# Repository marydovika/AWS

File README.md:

//////////////////////////////////////////////////////////////////////////////////////////////////

System Description:

Automatic Weather Stations (AWS) play a critical role in environmental monitoring, yet
their deployment in remote and energy-constrained locations remains limited by rigid and
monolithic power architectures.
Conventional systems are often designed for single energy sources, leading to inefficiencies, frequent power interruptions, high maintenance costs, and
poor adaptability to dynamic environmental conditions.
This research proposes the development of a modular and adaptive power electronics system architecture tailored for
energy-constrained AWS deployments.
Modular design;
The modular design introduces swappable converter topologies that allow scalable integration (multiplexing) of multiple energy sources,
including solar, DC input and  batteries, while simplifying upgrades, repairs, and fault isolation.
Adaptive design;
Complementing the modular design, an adaptive control strategy will be implemented to dynamically
optimize power flow in response to load variations, energy resource intermittency, in-system parameter drifts, and external/environmental
disturbances, thereby enhancing system stability and efficiency.
The study will involve system design, prototype development, and two algorithm development (both AMPC-based), followed by performance evaluation
under varying operating conditions and benchmarking. Field deployment of Final product (PCB, Case Unit, and Mounting frame).

Expected outcomes include;
improved system energy efficiency,
fault tolerance, and operational autonomy,
ensuring more reliable and sustainable weather data collection in energy resource-constrained and off-grid regions.
The findings of this research will contribute to advancing resilient power system solutions that support agriculture, public
safety, infrastructure planning, and climate research. with a civil and possible military adaptation.

Project is funded by:
https://www.ademneaproject.net

//////////////////////////////////////////////////////////////////////////////////////////////////

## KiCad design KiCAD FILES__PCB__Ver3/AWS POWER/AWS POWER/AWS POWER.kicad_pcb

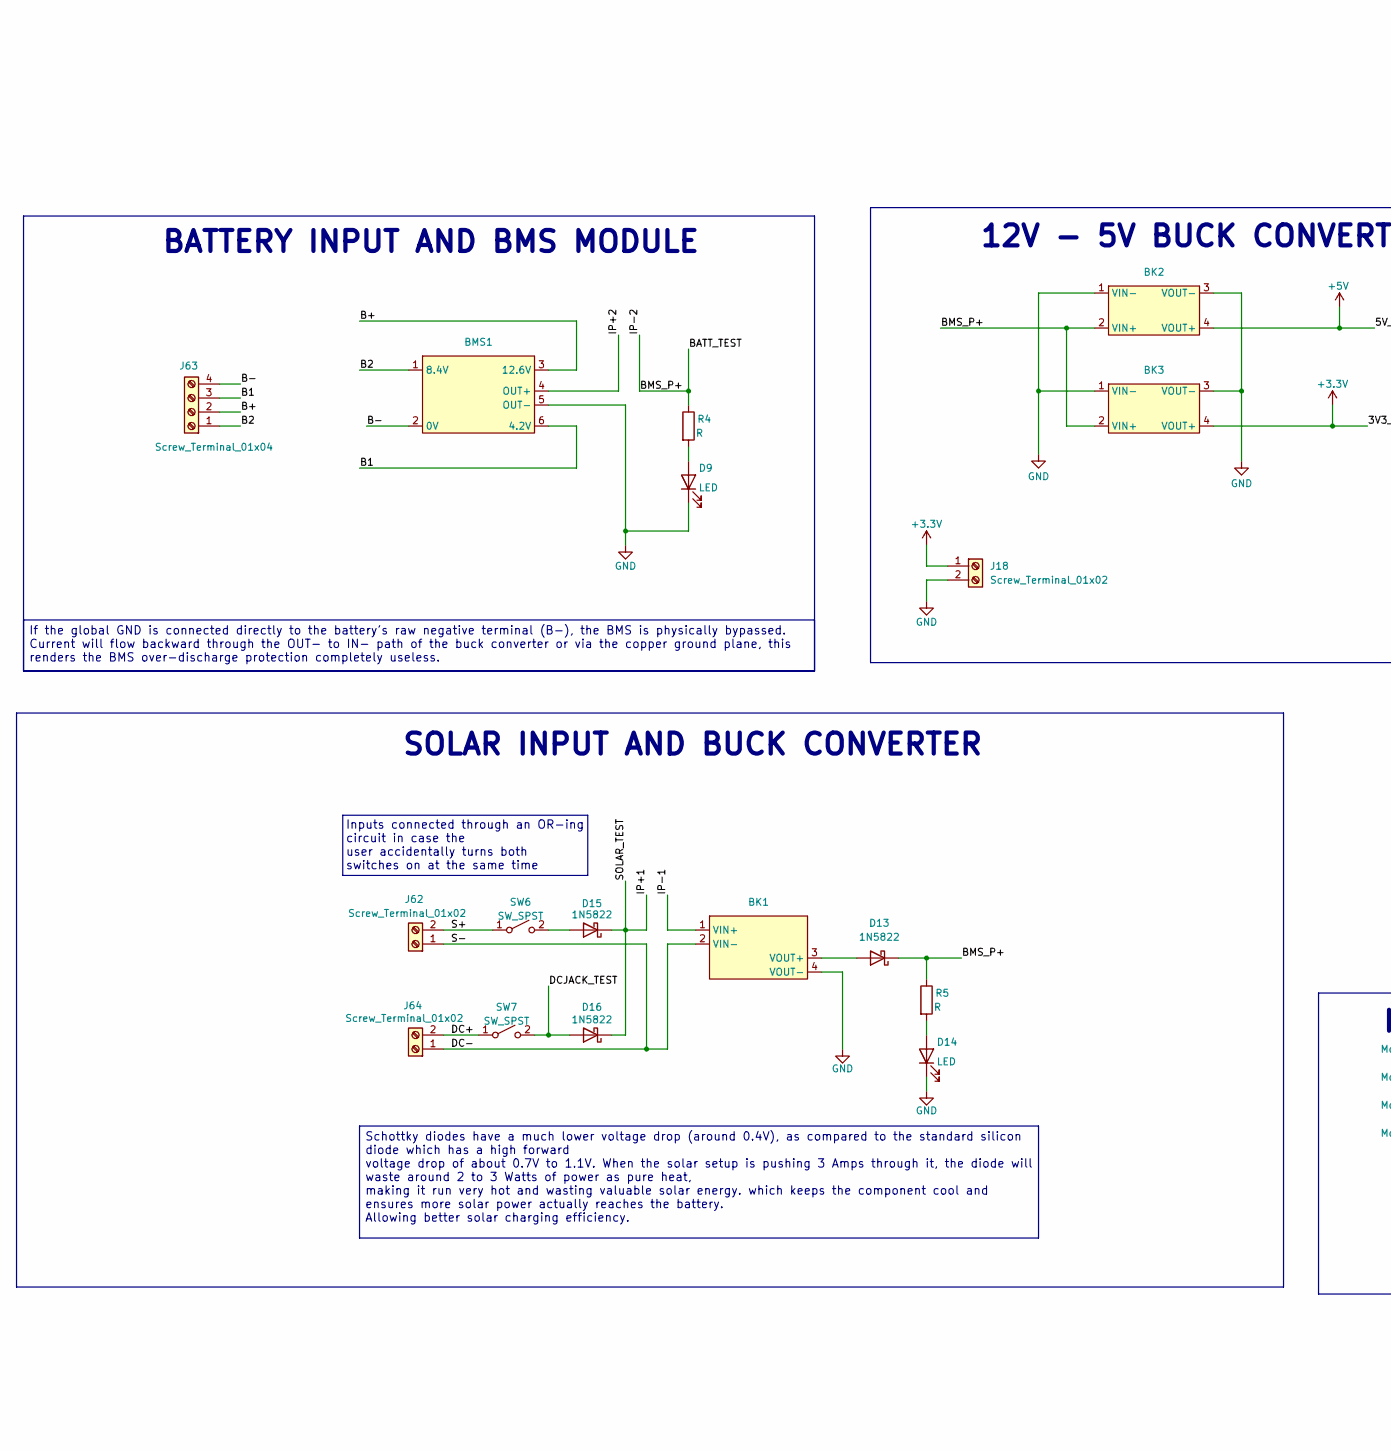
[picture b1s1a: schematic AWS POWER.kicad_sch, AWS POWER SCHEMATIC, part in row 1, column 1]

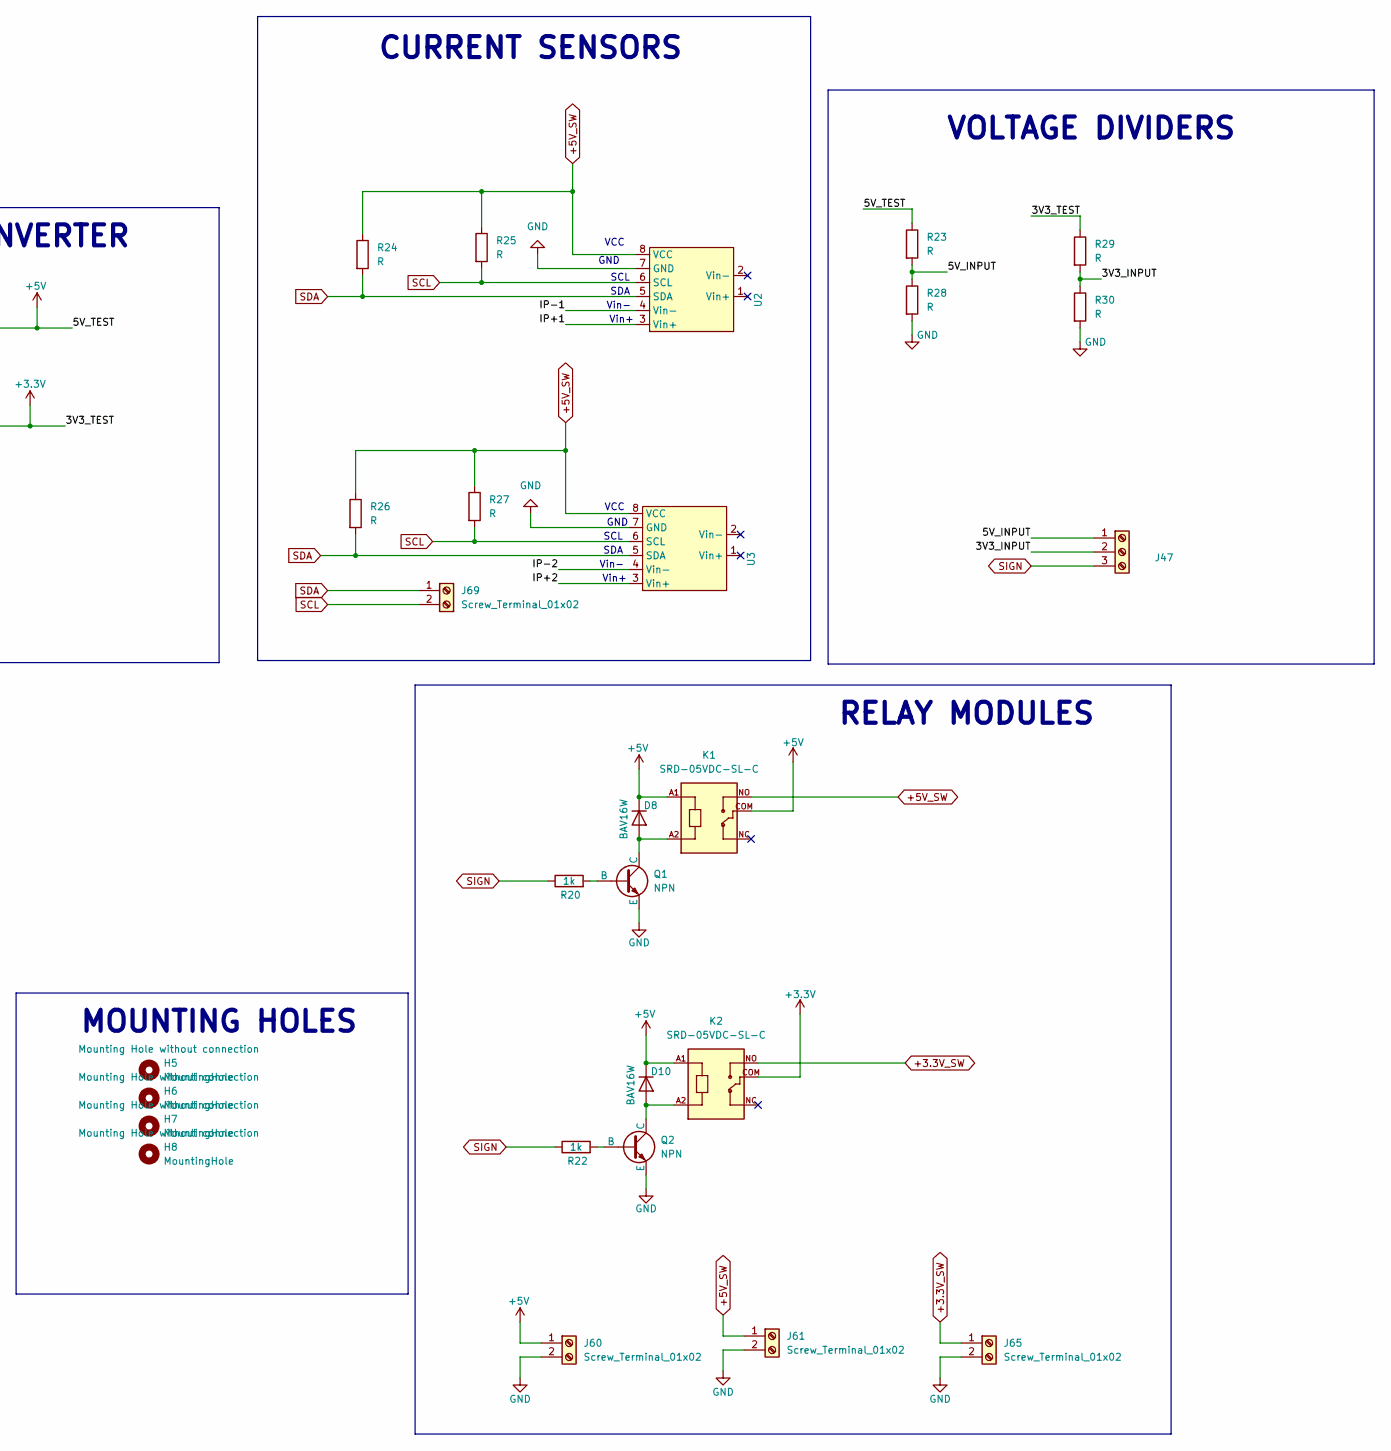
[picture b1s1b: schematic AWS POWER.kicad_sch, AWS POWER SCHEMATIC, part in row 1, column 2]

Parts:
BK1: cn4015-2_module
BK2, BK3: MP1584 MODULE
BMS1: 3S 40A BMS
D8, D10: BAV16W; D_DO-201AD_P15.24mm_Horizontal; LCSC C459527
D9, D14: LED; LED_D3.0mm
D13, D15, D16: 1N5822; D_DO-201AD_P15.24mm_Horizontal
H5, H6, H7, H8: MountingHole; MountingHole_3.2mm_M3_DIN965_Pad_TopOnly
J18, J60, J61, J62, J64, J65, J69: Screw_Terminal_01x02; TerminalBlock_MetzConnect_Type055_RT01502HDWU_1x02_P5.00mm_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
J47: Screw_Terminal_01x03; TerminalBlock_Phoenix_MKDS-1-3-3.81_1x03_P3.81mm_Horizontal
J63: Screw_Terminal_01x04; TerminalBlock_MetzConnect_Type055_RT01504HDWU_1x04_P5.00mm_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
K1, K2: SRD-05VDC-SL-C; RELAY_SRD-05VDC-SL-C; LCSC C35449
Q1, Q2: NPN; TO-92; LCSC C52801
R4, R5, R23, R24, R25, R26, R27, R28, R29, R30: R; R_Axial_DIN0207_L6.3mm_D2.5mm_P7.62mm_Horizontal
R20, R22: 1k; R_Axial_DIN0207_L6.3mm_D2.5mm_P7.62mm_Horizontal; LCSC C22548
SW6, SW7: SW_SPST; SW_DIP_SPSTx01_Slide_9.78x4.72mm_W7.62mm_P2.54mm
U2, U3: INA219 MODULE

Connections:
+3.3V: BK3.4 (VOUT+), J18.1, K2.COM, R29.1
+3.3V_SW: J65.1, K2.NO
+5V: BK2.4 (VOUT+), D8.1 (K), D10.1 (K), J60.1, K1.A1, K1.COM, K2.A1, R23.1
+5V_SW: J61.1, K1.NO, R24.1, R25.1, R26.1, R27.1, U2.8 (VCC), U3.8 (VCC)
/3V3_INPUT: J47.2, R29.2, R30.1
/5V_INPUT: J47.1, R23.2, R28.1
/B1: BMS1.6 (4.2V), J63.3
/B2: BMS1.1 (8.4V), J63.1
/B+: BMS1.3 (12.6V), J63.2
/B-: BMS1.2 (0V), J63.4
/BATT_TEST: BK2.2 (VIN+), BK3.2 (VIN+), D13.1 (K), R4.1, R5.1, U3.4 (Vin-)
/DC+: J64.2, SW7.1 (A)
/DC-: BK1.2 (VIN-), J62.1, J64.1
/DCJACK_TEST: D16.2 (A), SW7.2 (B)
/IP+1: D15.1 (K), D16.1 (K), U2.3 (Vin+)
/IP+2: BMS1.4 (OUT+), U3.3 (Vin+)
/IP-1: BK1.1 (VIN+), U2.4 (Vin-)
/S+: J62.2, SW6.1 (A)
GND: BK1.4 (VOUT-), BK2.1 (VIN-), BK2.3 (VOUT-), BK3.1 (VIN-), BK3.3 (VOUT-), BMS1.5 (OUT-), D9.1 (K), D14.1 (K), J18.2, J60.2, J61.2, J65.2, Q1.3 (E), Q2.3 (E), R28.2, R30.2, U2.7 (GND), U3.7 (GND)
unnamed: BK1.3 (VOUT+), D13.2 (A)
unnamed: D8.2 (A), K1.A2, Q1.1 (C)
unnamed: D9.2 (A), R4.2
unnamed: D10.2 (A), K2.A2, Q2.1 (C)
unnamed: D14.2 (A), R5.2
unnamed: D15.2 (A), SW6.2 (B)
unnamed: Q1.2 (B), R20.2
unnamed: Q2.2 (B), R22.2
SCL: J69.2, R25.2, R27.2, U2.6 (SCL), U3.6 (SCL)
SDA: J69.1, R24.2, R26.2, U2.5 (SDA), U3.5 (SDA)
SIGN: J47.3, R20.1, R22.1

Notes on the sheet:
SCL
CURRENT SENSORS
Inputs connected through an OR-ing circuit in case the user accidentally turns both switches on at the same time
MOUNTING HOLES
BATTERY INPUT AND BMS MODULE
VOLTAGE DIVIDERS
GND
SOLAR INPUT AND BUCK CONVERTER
SDA
VCC
Vin-
Vin+
RELAY MODULES
12V - 5V BUCK CONVERTER
Schottky diodes have a much lower voltage drop (around 0.4V), as compared to the standard silicon diode which has a high forward voltage drop of about 0.7V to 1.1V. When the solar setup is pushing 3 Amps through it, the diode will waste around 2 to 3 Watts of power as pure heat, making it run very 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
If the global GND is connected directly to the battery's raw negative terminal (B-), the BMS is physically bypassed. Current will flow backward through the OUT- to IN- path of the buck converter or via the copper ground plane, this renders the BMS over-discharge protection completely useless.

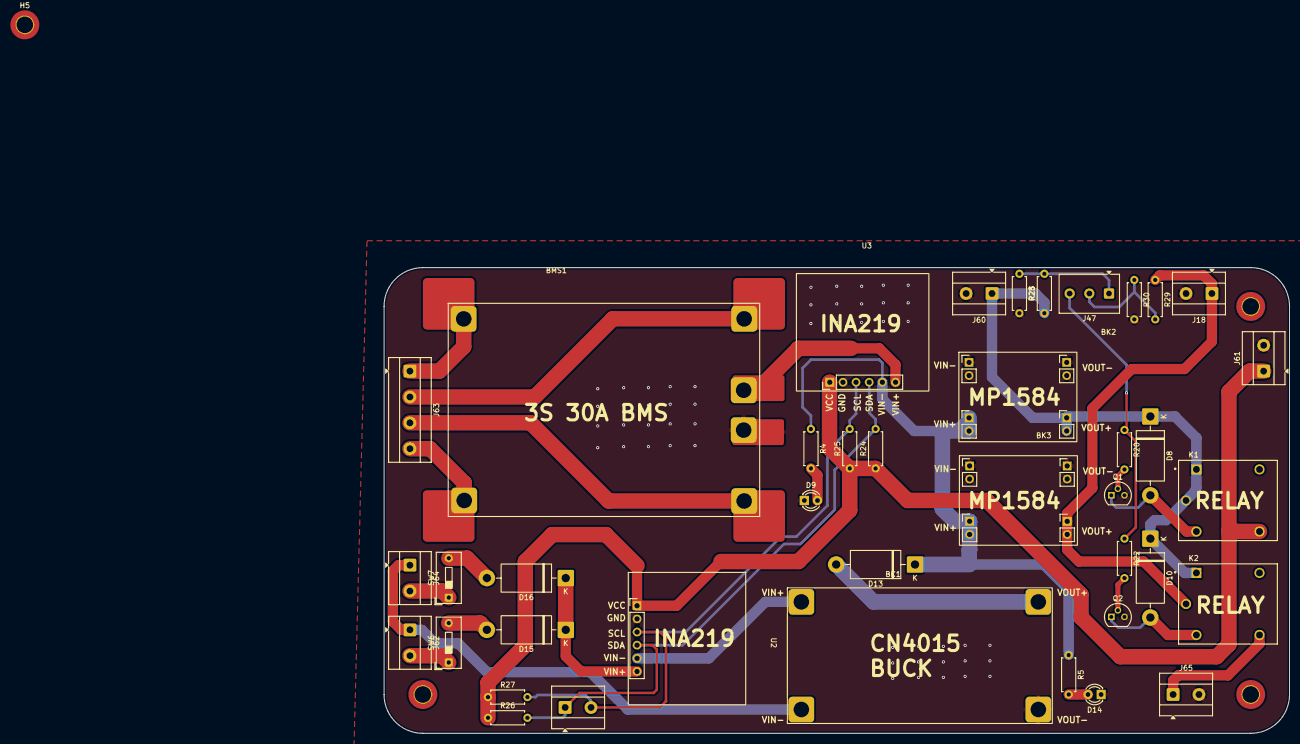
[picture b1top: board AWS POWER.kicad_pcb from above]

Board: 2 copper layers, 175.0 x 90.0 mm, 44 parts (0 on the bottom side), 30 nets.

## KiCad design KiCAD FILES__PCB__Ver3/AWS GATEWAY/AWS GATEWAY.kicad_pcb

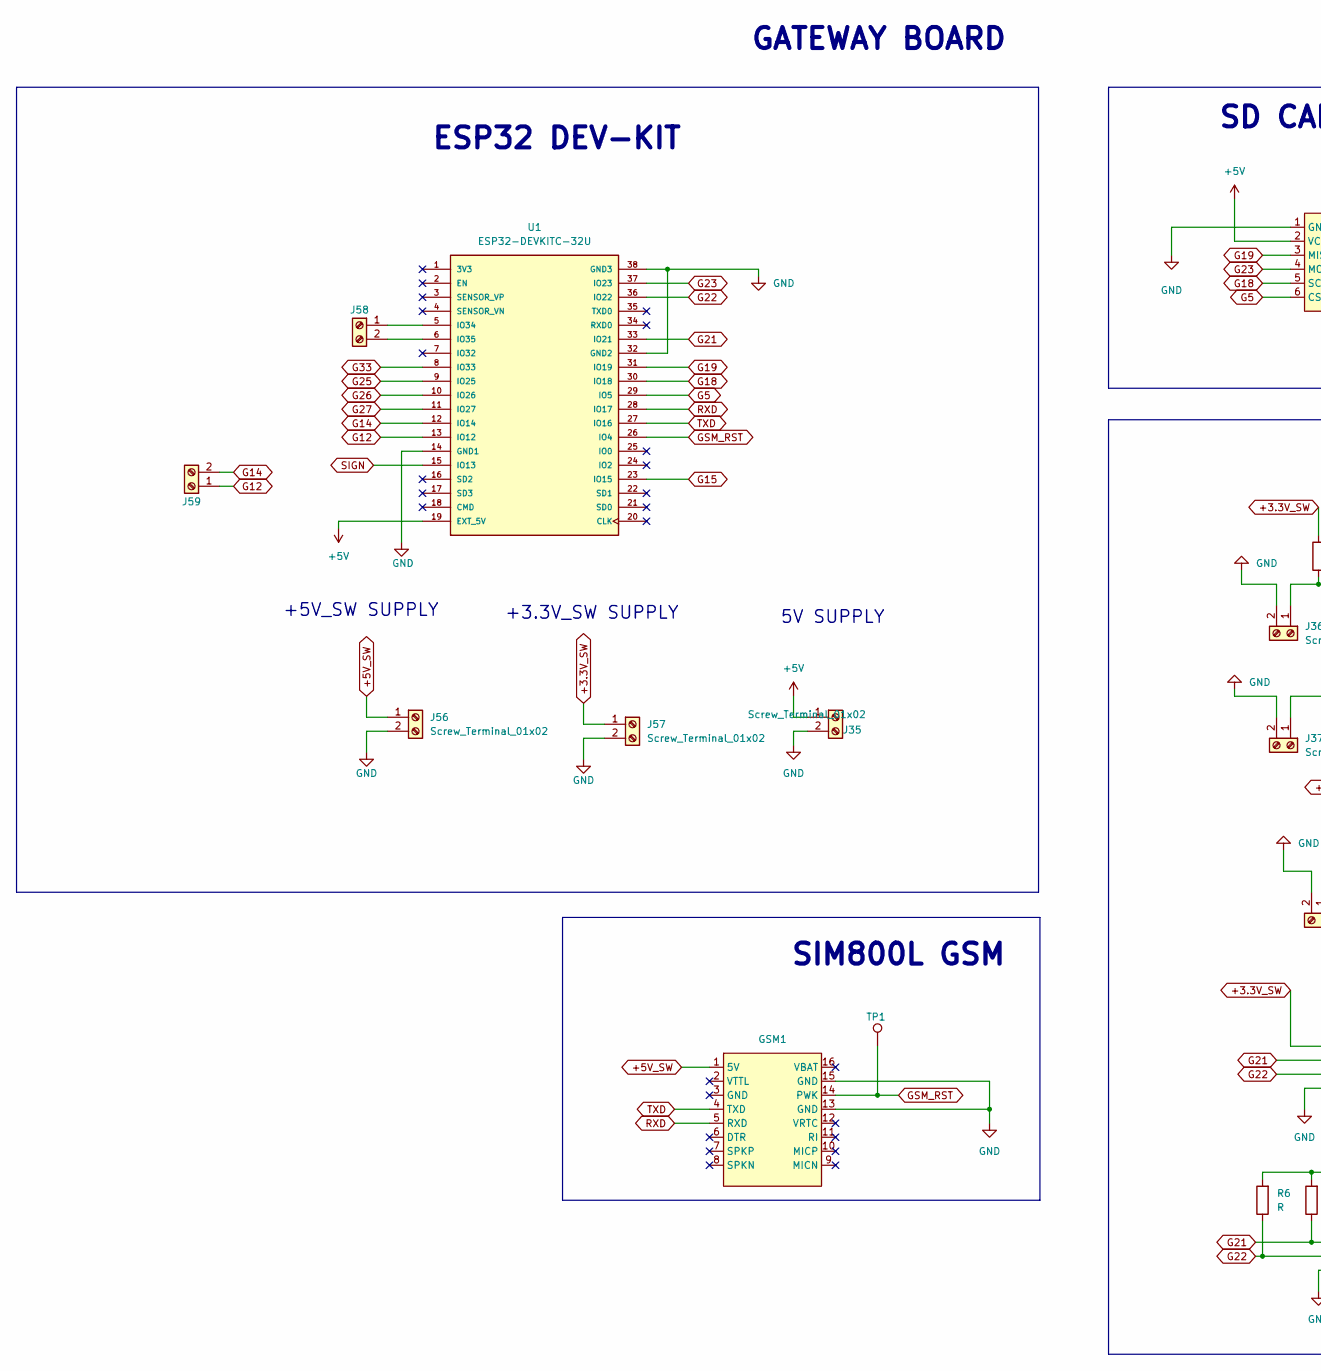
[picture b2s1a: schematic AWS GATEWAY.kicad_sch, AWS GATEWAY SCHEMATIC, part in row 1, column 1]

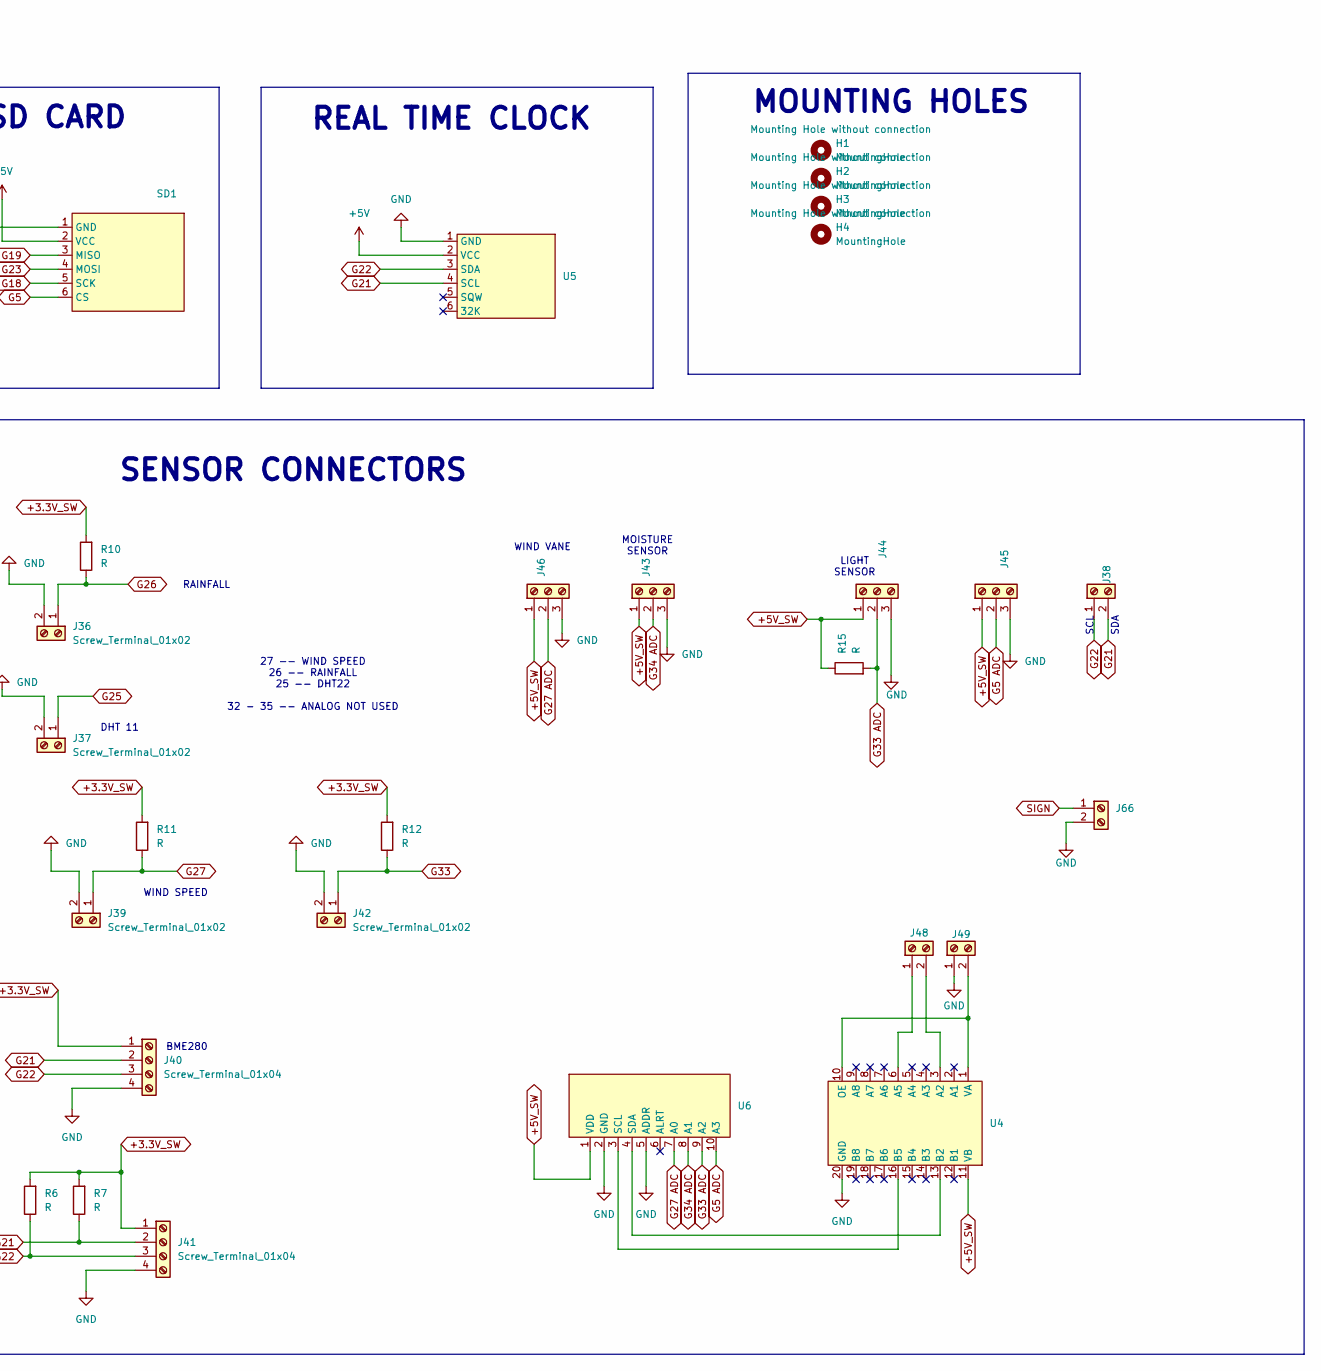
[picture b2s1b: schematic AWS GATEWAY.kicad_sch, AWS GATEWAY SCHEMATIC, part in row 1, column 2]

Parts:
GSM1: GSM MODULE
H1, H2, H3, H4: MountingHole; MountingHole_3.2mm_M3_DIN965_Pad_TopOnly
J35, J36, J37, J38, J39, J42, J48, J49: Screw_Terminal_01x02; TerminalBlock_Phoenix_MKDS-1-2-3.81_1x02_P3.81mm_Horizontal
J40, J41: Screw_Terminal_01x04; TerminalBlock_Phoenix_MKDS-1-4-3.81_1x04_P3.81mm_Horizontal
J43, J44, J45, J46: Screw_Terminal_01x03; TerminalBlock_Phoenix_MKDS-1-3-3.81_1x03_P3.81mm_Horizontal
J56, J57, J58, J59, J66: Screw_Terminal_01x02; TerminalBlock_MetzConnect_Type055_RT01502HDWU_1x02_P5.00mm_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
R6, R7, R10, R11, R12, R15: R; R_Axial_DIN0204_L3.6mm_D1.6mm_P7.62mm_Horizontal
SD1: SD CARD MODULE
TP1: TestPoint; TestPoint_Pad_D3.0mm
U1: ESP32-DEVKITC-32U; MODULE_ESP32-DEVKITC-32U; PARTREV V4
U4: logic level shifter
U5: RTC MODULE
U6: ADS115 MODULE

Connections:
+3.3V_SW: J40.1, J41.1, J57.1, R6.2, R7.2, R10.2, R11.2, R12.2
+5V: J35.1, SD1.2 (VCC), U1.19 (EXT_5V), U5.2 (VCC)
+5V_SW: GSM1.1 (5V), J43.1, J44.1, J45.1, J46.1, J56.1, R15.1, U4.11 (VB), U6.1 (VDD)
G5: SD1.6 (CS), U1.29 (IO5)
G5 ADC: J45.2, U6.10 (A3)
G12: J59.1, U1.13 (IO12)
G14: J59.2, U1.12 (IO14)
G15: U1.23 (IO15)
G18: SD1.5 (SCK), U1.30 (IO18)
G19: SD1.3 (MISO), U1.31 (IO19)
G21: J38.2, J40.2, J41.2, R7.1, U1.33 (IO21), U5.4 (SCL)
G22: J38.1, J40.3, J41.3, R6.1, U1.36 (IO22), U5.3 (SDA)
G23: SD1.4 (MOSI), U1.37 (IO23)
G25: J37.1, U1.9 (IO25)
G26: J36.1, R10.1, U1.10 (IO26)
G27: J39.1, R11.1, U1.11 (IO27)
G27 ADC: J46.2, U6.7 (A0)
G33: J42.1, R12.1, U1.8 (IO33)
G33 ADC: J44.2, R15.2, U6.9 (A2)
G34 ADC: J43.2, U6.8 (A1)
GND: GSM1.13 (GND), GSM1.15 (GND), J35.2, J36.2, J37.2, J39.2, J40.4, J41.4, J42.2, J43.3, J44.3, J45.3, J46.3, J49.1, J56.2, J57.2, J66.2, SD1.1 (GND), U1.14 (GND1), U1.32 (GND2), U1.38 (GND3), U4.20 (GND), U5.1 (GND), U6.2 (GND), U6.5 (ADDR)
GSM_RST: GSM1.14 (PWK), TP1.1 (1_1), U1.26 (IO4)
unnamed: J48.1, U4.6 (A5)
unnamed: J48.2, U4.3 (A2)
unnamed: J49.2, U4.1 (VA), U4.10 (OE)
unnamed: J58.1, U1.5 (IO34)
unnamed: J58.2, U1.6 (IO35)
unnamed: U4.13 (B2), U6.4 (SDA)
unnamed: U4.16 (B5), U6.3 (SCL)
RXD: GSM1.5 (RXD), U1.28 (IO17)
SIGN: J66.1, U1.15 (IO13)
TXD: GSM1.4 (TXD), U1.27 (IO16)

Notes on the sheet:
GATEWAY BOARD
SENSOR CONNECTORS
MOUNTING HOLES
+5V_SW SUPPLY
SDA
MOISTURE SENSOR
SD CARD
RAINFALL
WIND VANE
LIGHT SENSOR
WIND SPEED
SCL
BME280
27 -- WIND SPEED 26 -- RAINFALL 25 -- DHT22 32 - 35 -- ANALOG NOT USED
DHT 11
REAL TIME CLOCK
ESP32 DEV-KIT
+3.3V_SW SUPPLY
5V SUPPLY
SIM800L GSM

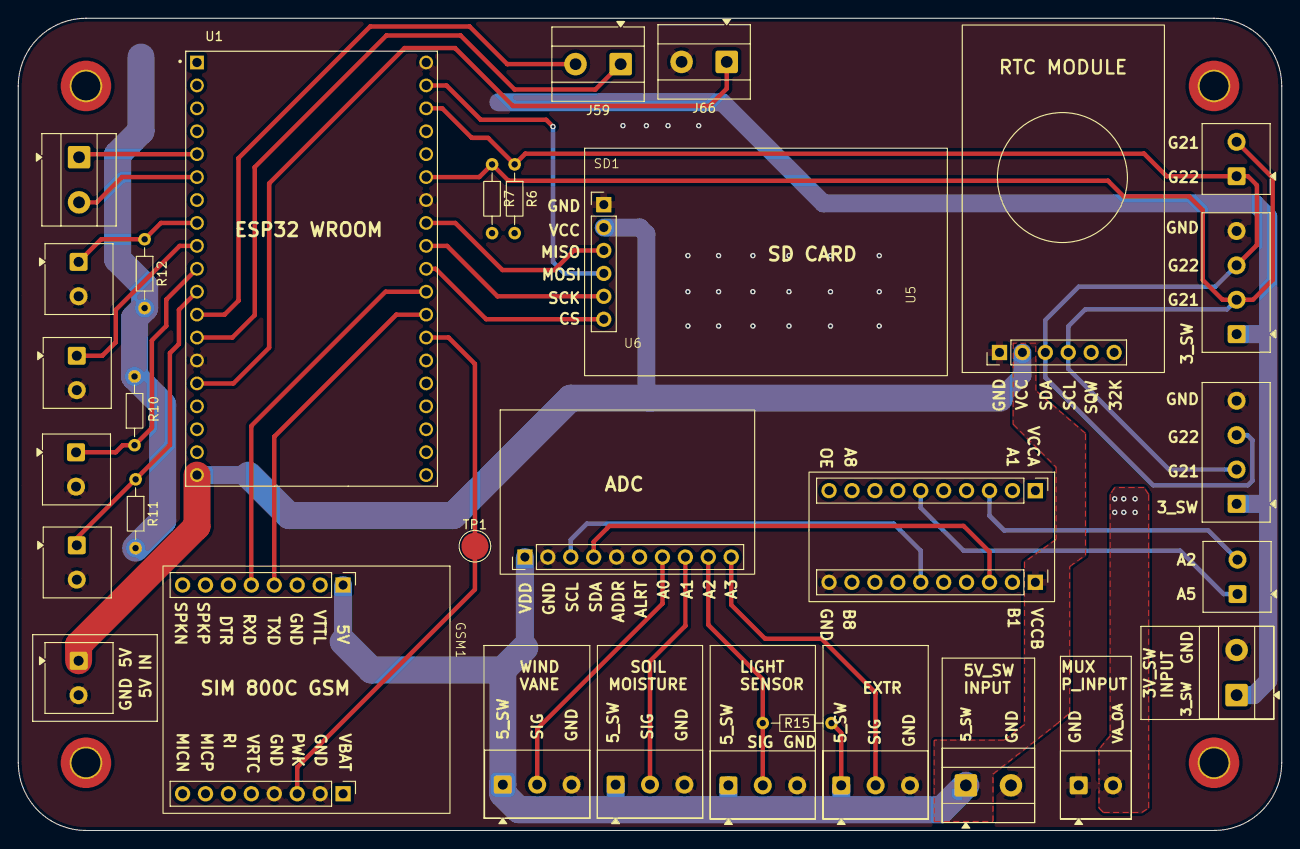
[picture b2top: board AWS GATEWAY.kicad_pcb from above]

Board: 2 copper layers, 140.0 x 90.0 mm, 36 parts (0 on the bottom side), 31 nets.

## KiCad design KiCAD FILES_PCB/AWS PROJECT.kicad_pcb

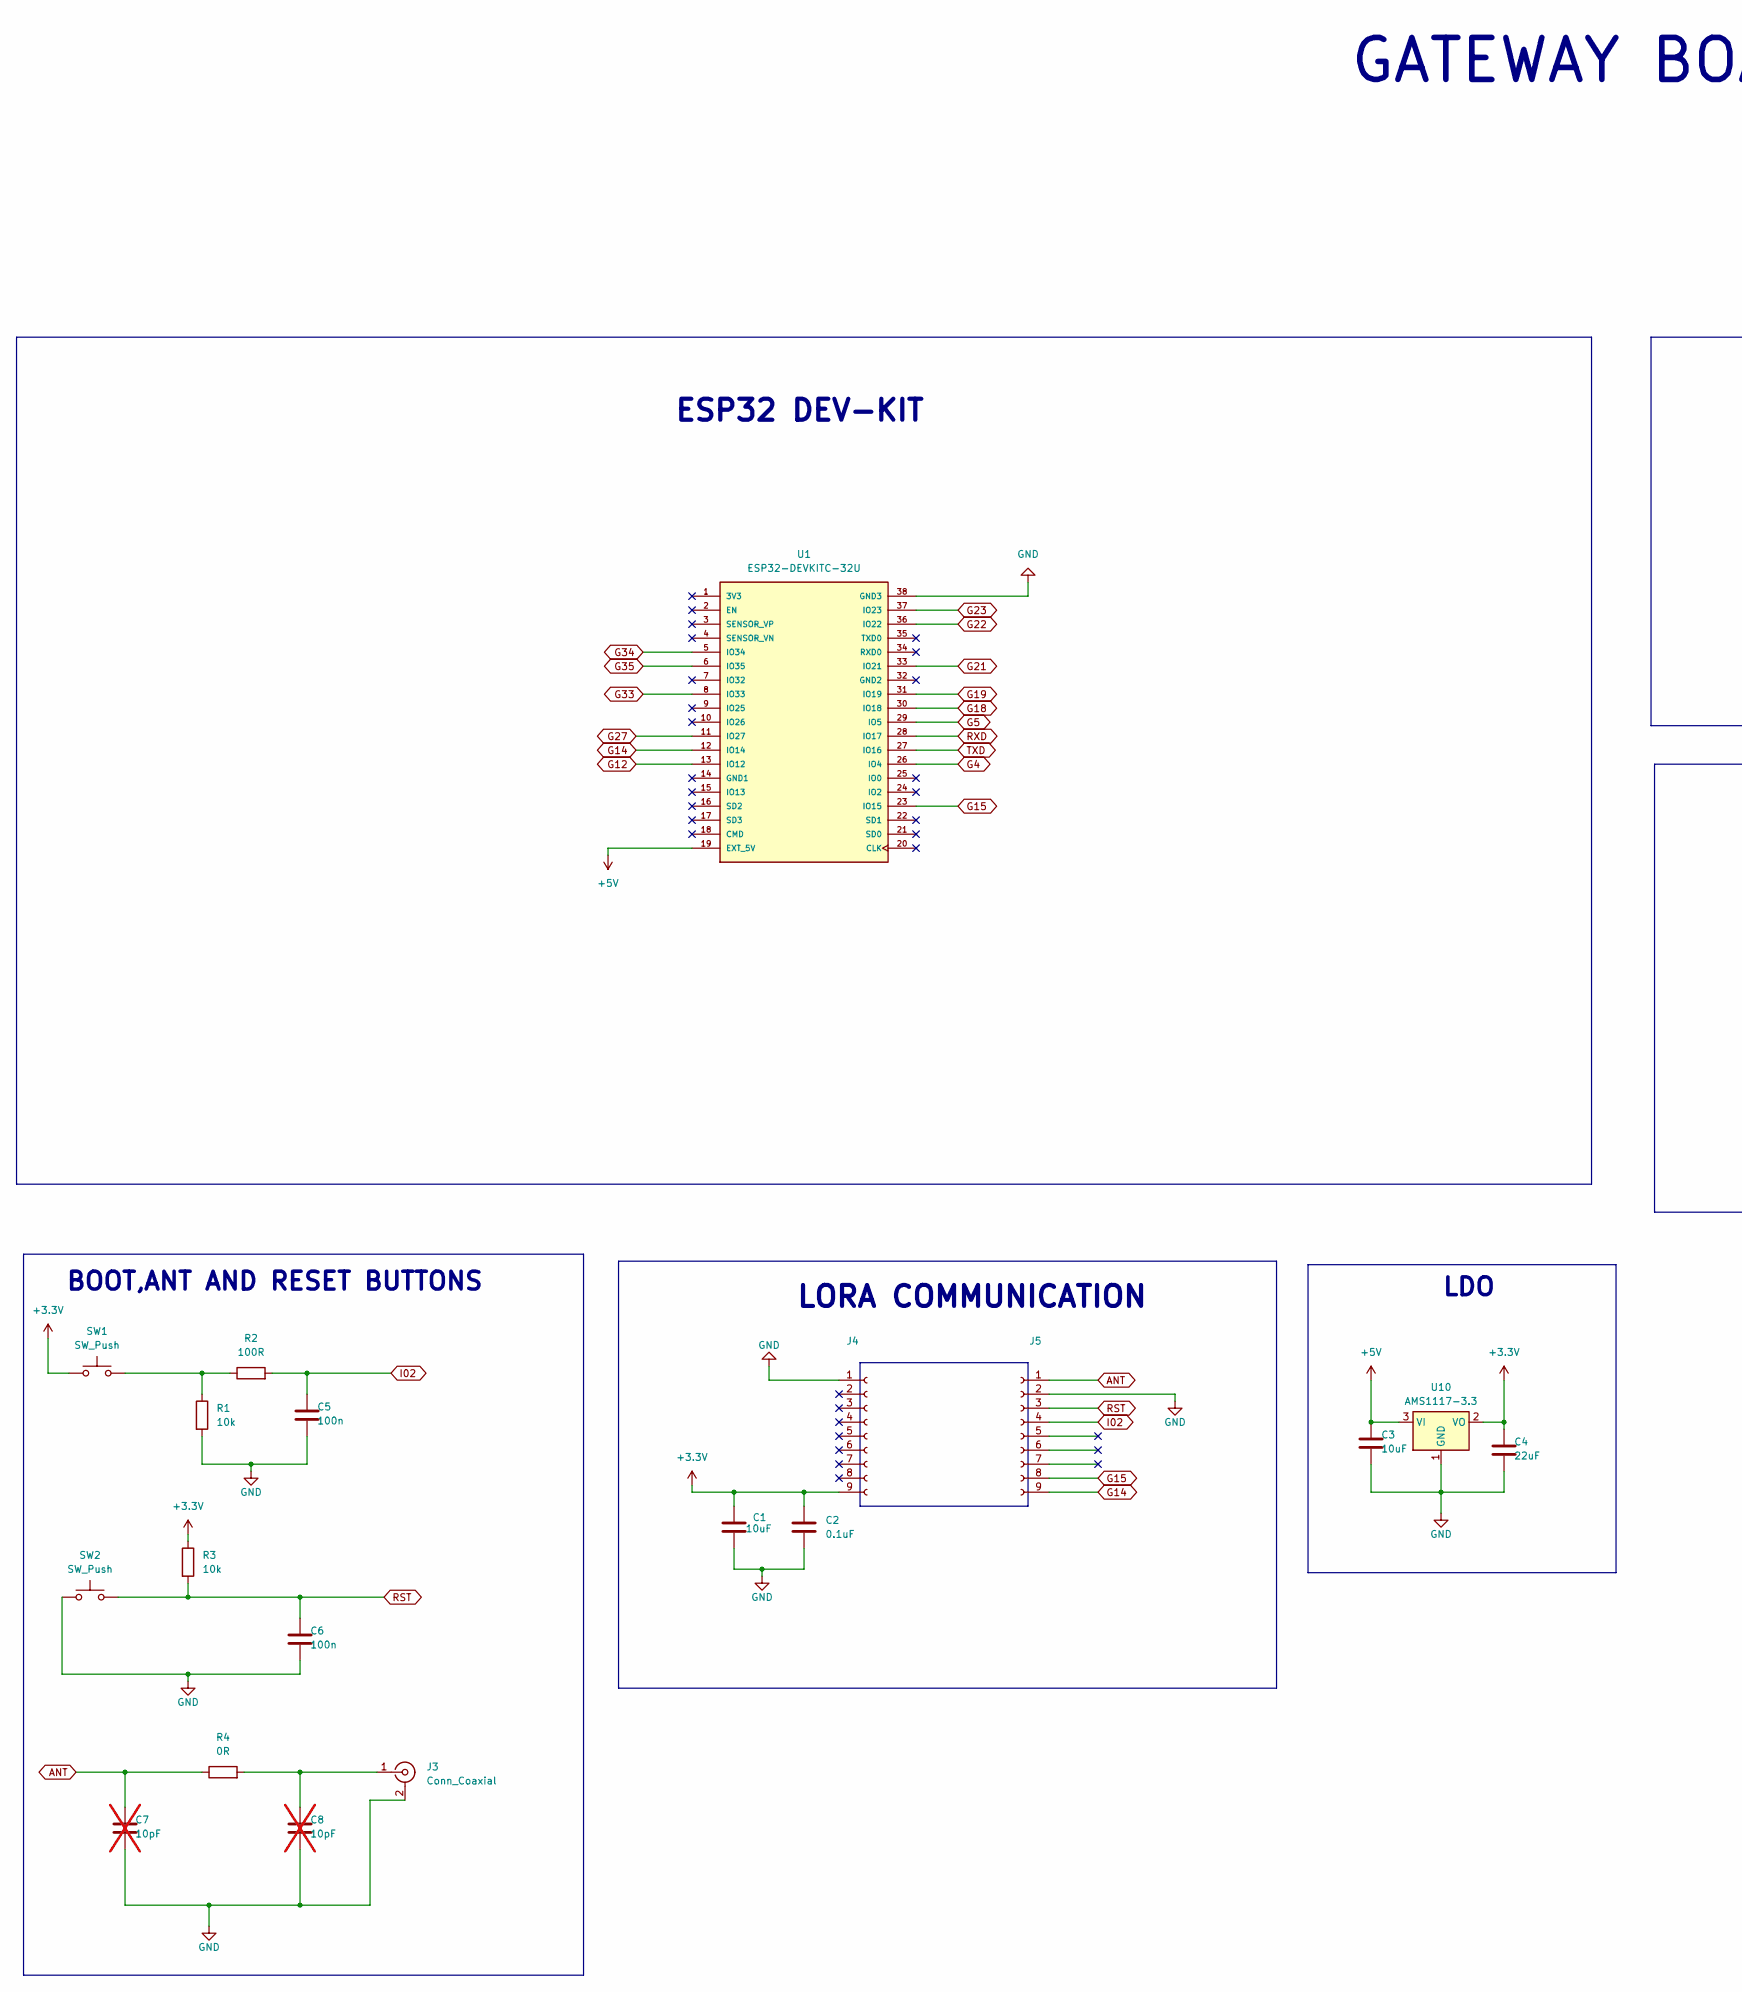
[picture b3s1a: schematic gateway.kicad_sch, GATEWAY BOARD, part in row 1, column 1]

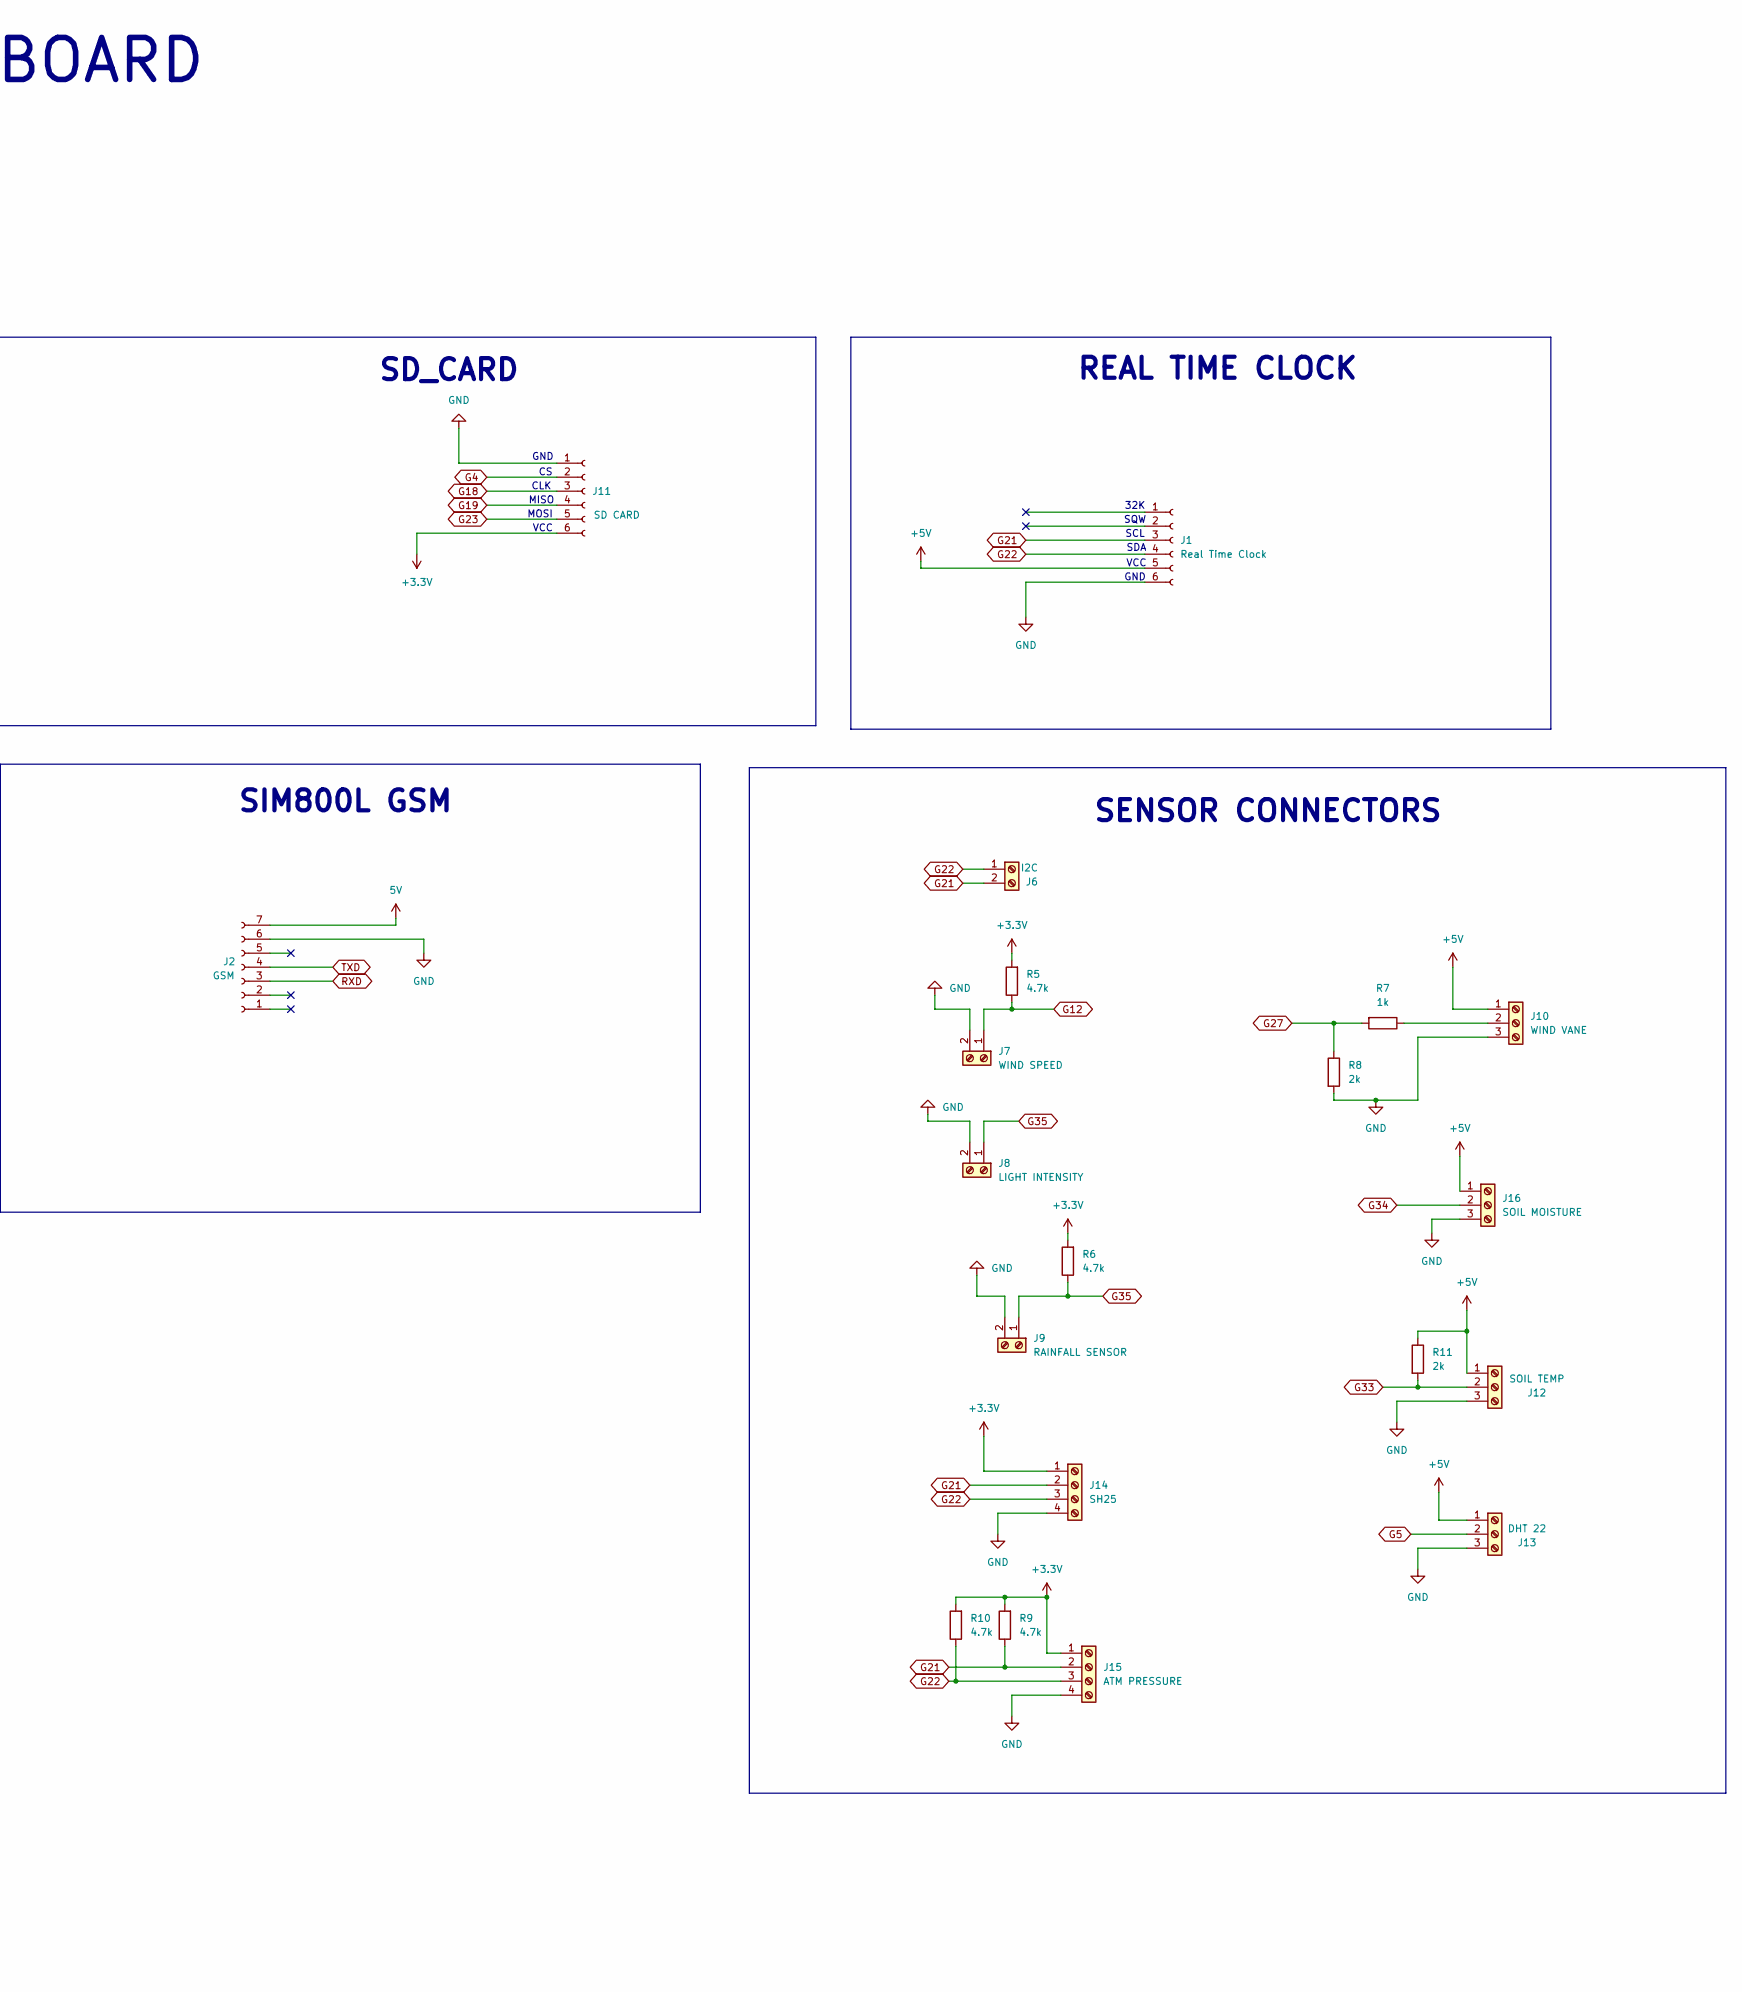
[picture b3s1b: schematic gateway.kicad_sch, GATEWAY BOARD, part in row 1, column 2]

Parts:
C1, C3: 10uF; CP_Radial_D10.0mm_P7.50mm
C2: 0.1uF; CP_Radial_D10.0mm_P7.50mm
C4: 22uF; CP_Radial_D10.0mm_P7.50mm
C5, C6: 100n; CP_Radial_D10.0mm_P7.50mm
C7, C8: 10pF; C_0402_1005Metric_Pad0.74x0.62mm_HandSolder; not fitted
J1: Real Time Clock; Molex_SPOX_5267-06A_1x06_P2.50mm_Vertical
J2: GSM; Molex_SPOX_5267-07A_1x07_P2.50mm_Vertical
J3: Conn_Coaxial; U.FL_Molex_MCRF_73412-0110_Vertical
J4, J5: Conn_01x09_Socket; PinSocket_1x09_P2.54mm_Vertical
J6: I2C; TerminalBlock_Phoenix_MKDS-1-2-3.81_1x02_P3.81mm_Horizontal
J7: WIND SPEED; TerminalBlock_Phoenix_MKDS-1-2-3.81_1x02_P3.81mm_Horizontal
J8: LIGHT INTENSITY; TerminalBlock_Phoenix_MKDS-1-2-3.81_1x02_P3.81mm_Horizontal
J9: RAINFALL SENSOR; TerminalBlock_Phoenix_MKDS-1-2-3.81_1x02_P3.81mm_Horizontal
J10: WIND VANE; TerminalBlock_Phoenix_MKDS-1-3-3.81_1x03_P3.81mm_Horizontal
J11: SD CARD; Molex_SPOX_5267-06A_1x06_P2.50mm_Vertical
J12: SOIL TEMP; TerminalBlock_Phoenix_MKDS-1-3-3.81_1x03_P3.81mm_Horizontal
J13: DHT 22; TerminalBlock_Phoenix_MKDS-1-3-3.81_1x03_P3.81mm_Horizontal
J14: SH25; TerminalBlock_Phoenix_MKDS-1-4-3.81_1x04_P3.81mm_Horizontal
J15: ATM PRESSURE; TerminalBlock_Phoenix_MKDS-1-4-3.81_1x04_P3.81mm_Horizontal
J16: SOIL MOISTURE; TerminalBlock_Phoenix_MKDS-1-3-3.81_1x03_P3.81mm_Horizontal
R1, R3: 10k; R_Axial_DIN0204_L3.6mm_D1.6mm_P5.08mm_Horizontal
R2: 100R; R_Axial_DIN0204_L3.6mm_D1.6mm_P5.08mm_Horizontal
R4: 0R; R_0805_2012Metric
R5, R6, R9, R10: 4.7k; R_0805_2012Metric
R7: 1k; R_0805_2012Metric
R8, R11: 2k; R_0805_2012Metric
SW1, SW2: SW_Push; SW_PUSH_6mm_H4.3mm
U1: ESP32-DEVKITC-32U; MODULE_ESP32-DEVKITC-32U; PARTREV V4
U10: AMS1117-3.3; SOT-223-3_TabPin2; LCSC C6186

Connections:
5V: J2.7
+3.3V: C1.1, C2.1, C4.1, J4.9, J11.6, J14.1, J15.1, R3.1, R5.2, R6.2, R9.2, R10.2, SW1.1, U10.2 (VO)
+5V: C3.1, J1.5, J10.1, J12.1, J13.1, J16.1, R11.1, U1.19 (EXT_5V), U10.3 (VI)
ANT: C7.1, J5.1, R4.1
G4: J11.2, U1.26 (IO4)
G5: J13.2, U1.29 (IO5)
G12: J7.1, R5.1, U1.13 (IO12)
G14: J5.9, U1.12 (IO14)
G15: J5.8, U1.23 (IO15)
G18: J11.3, U1.30 (IO18)
G19: J11.4, U1.31 (IO19)
G21: J1.3, J6.2, J14.2, J15.2, R9.1, U1.33 (IO21)
G22: J1.4, J6.1, J14.3, J15.3, R10.1, U1.36 (IO22)
G23: J11.5, U1.37 (IO23)
G27: R7.2, R8.1, U1.11 (IO27)
G33: J12.2, R11.2, U1.8 (IO33)
G34: J16.2, U1.5 (IO34)
G35: J8.1, J9.1, R6.1, U1.6 (IO35)
GND: C1.2, C2.2, C3.2, C4.2, C5.2, C6.2, C7.2, C8.2, J1.6, J2.6, J3.2 (Ext), J4.1, J5.2, J7.2, J8.2, J9.2, J10.3, J11.1, J12.3, J13.3, J14.4, J15.4, J16.3, R1.2, R8.2, SW2.1, U1.38 (GND3), U10.1 (GND)
I02: C5.1, J5.4, R2.2
unnamed: C8.1, J3.1 (In), R4.2
unnamed: J10.2, R7.1
unnamed: R1.1, R2.1, SW1.2
RST: C6.1, J5.3, R3.2, SW2.2
RXD: J2.3, U1.28 (IO17)
TXD: J2.4, U1.27 (IO16)

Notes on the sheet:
CLK
BOOT,ANT AND RESET BUTTONS
GATEWAY BOARD
SENSOR CONNECTORS
VCC
ESP32 DEV-KIT
GND
MISO
SDA
SIM800L GSM
LORA COMMUNICATION
32K
MOSI
SQW
SD_CARD
SCL
REAL TIME CLOCK
LDO

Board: 2 copper layers, 39 parts (0 on the bottom side), 25 nets, no tracks yet.
